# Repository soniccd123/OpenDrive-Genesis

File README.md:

# OpenDrive-Genesis
A open hardware flashcart for the Sega Genesis/32X

This project was born as way to use 3.3V parts safely for repro carts but, with the use o Flash memory, the read/write potencial of the ROM made me develop it to another direction: A Flashcart

This is quite a barebones Flashcart, nothing compared to Krizz's Everdrive ease of use. It is intended for DIY entusiasts, as learning platform and maybe as a starting point for me and other people projects. This is Open Hardware, do whatever it pleases you with it, I'm happy to help as needed.

As of now, these are its features:

- Suports Genesis and 32X software
- ROM Support for up to 4MB
- Save support for all ROM sizes (Selection for <2MB/>2MB by jumper)
- 32KB of FeRAM for saving
- No need for battery for saving
- Safe 3.3V to 5V level-shifting

What it doesnt do compared to commercially available carts:
- Multiple ROMs at the same time;
- ROM menu;
- SD support;
- Needs a programmer (The OpenDrive Programmer)
- Does not support Sega CD games and special chips (and probably never will);

This project is possible thanks to TmEE (NESdev Forums, SRAM wiring schematics), Rene Richard (db-electronics on GitHUB, KiCAD libs for the Genesis cart connector), lidnariq (NESdev Forums, Safe level-shifting), Ziggy587 (Racketboy, ideas, sugestions, support and encouragement), The Racketboy and NESdev forums.

# Other projects of the same family
- OpenDrive Programmer: https://github.com/soniccd123/OpenDrive-Programmer
- OpenDrive Programmer firmware: https://github.com/soniccd123/OpenDrive-Programmer-firmware
- OpenDrive Editor: https://github.com/soniccd123/OpenDrive-Editor

# Building the cartridge
I recommend that the release folder is used, the Bill of Materials is contained in the CSV file. The develop folder also works and its the actually tested cart by me, it only has aditional footprints for a being tested bank switching circuit.

The FM1808 is also not strictly necessary if you don't plan to save your games. The 74HC74 and the 74HC139 are still necessary in this case for the correct CE signaling.

You must short the JP1 jumper acordinly to the type of games you're going to use:
- For save support on <2MB games, short pins 1 and 2 (<2MB on the cart);
- For save support on >2MB games, short pins 3 and 2 (>2MB on the cart);
- If the save support is not necessary and the FM1808 is not soldered, short the 3 and 2 pins (>2MB on the cart).

With this the cart should be ready for writing and playing!

# Documentation
- Technical Manual, in constant work, sugestions welcome: https://docs.google.com/document/d/e/2PACX-1vTHuY665FCTQgpWVqtx0Hk3dTyNgIxMEns0RzGF2l86pw4OjIR6taxs3owxL13b5aOQaE71-1f7qCdJ/pub
- MX29L3211 Datasheet: http://www.wolfgangrobel.de/electronics/datasheets/eprom/MX29L3211.pdf
- FM1808 Datasheet: https://datasheet.octopart.com/FM1808-70-PG-Ramtron-datasheet-8328945.pdf
- 74HC74 Datasheet: https://assets.nexperia.com/documents/data-sheet/74HC_HCT74.pdf
- 74HC139 Datasheet https://assets.nexperia.cn/documents/data-sheet/74HC_HCT139.pdf
- 74LVC8T245 Datasheet: https://assets.nexperia.com/documents/data-sheet/74LVC_LVCH8T245.pdf

# Disclaimer
I'm not a professional hardware engineer, while this flashcart was designed to be the safest possible to your console, I'm not responsible for any damages done if used or built wrong. Also, revise the design always before building the PCB, I'm a amateur human and errors may have been commited. It you spot anything, hit me with a message and I will happily fix that. Also, any sugestions are welcome!

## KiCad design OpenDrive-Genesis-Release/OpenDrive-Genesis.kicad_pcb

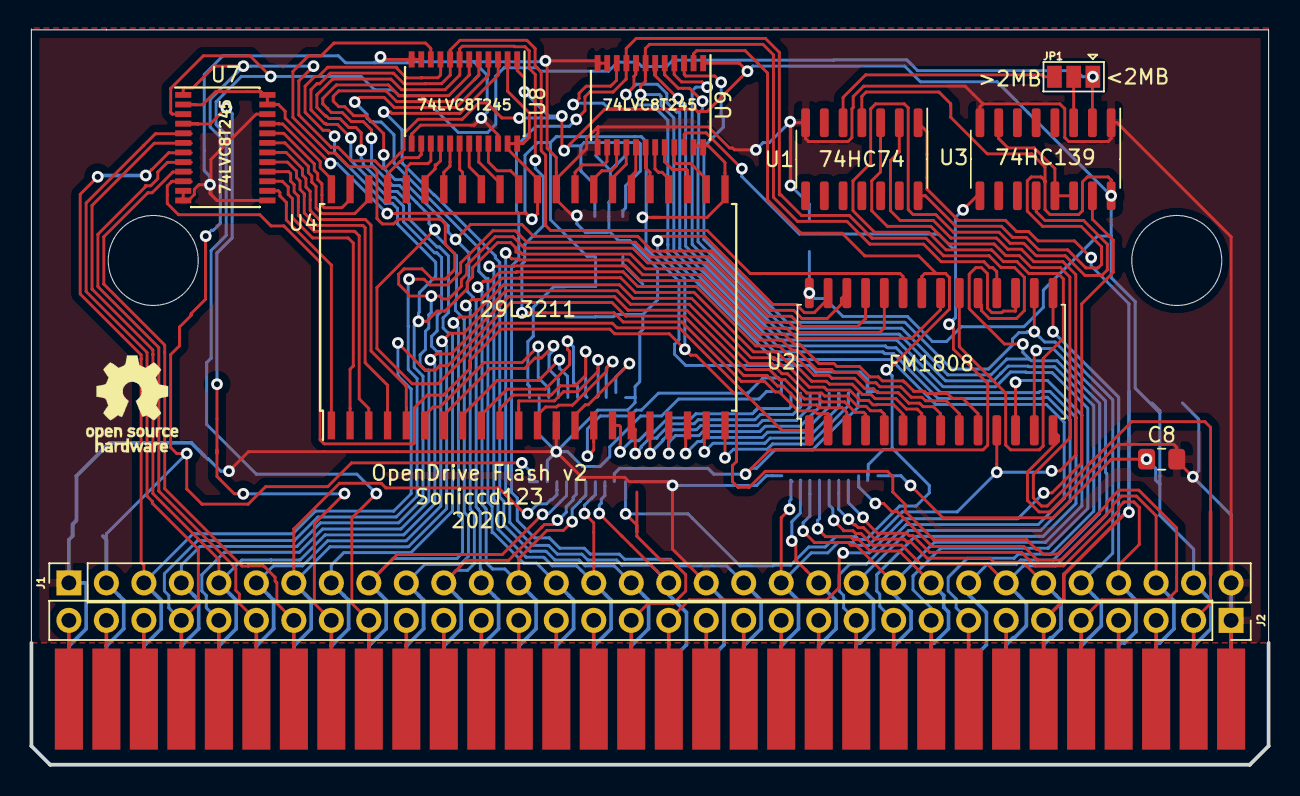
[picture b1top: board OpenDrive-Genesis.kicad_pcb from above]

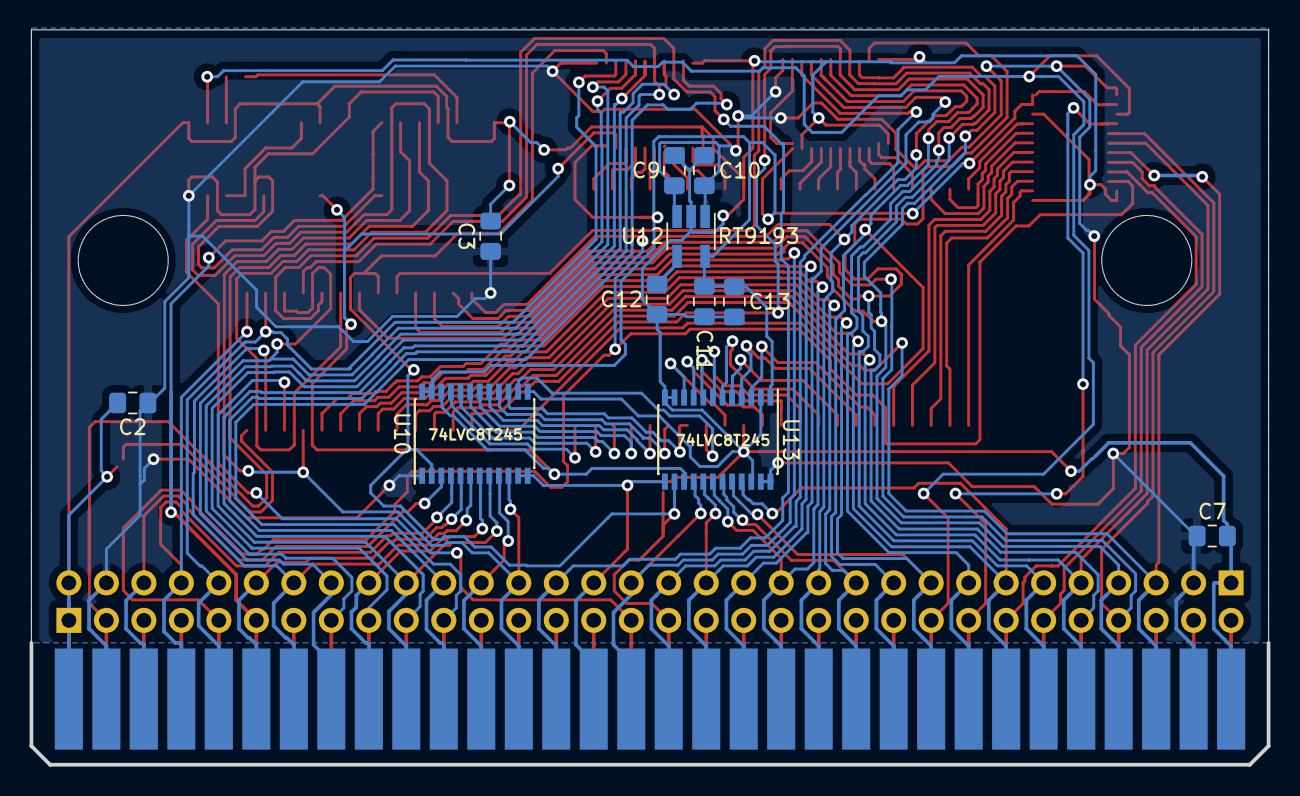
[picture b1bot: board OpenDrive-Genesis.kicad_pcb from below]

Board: 2 copper layers, 83.8 x 49.7 mm, 23 parts (11 on the bottom side), 107 nets.

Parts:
C2, C3, C7, C8, C9, C13: 100nF; C_0805_2012Metric_Pad1.15x1.40mm_HandSolder
C10, C11: 10uF; C_0805_2012Metric_Pad1.15x1.40mm_HandSolder
C12: 1uF; C_0805_2012Metric_Pad1.15x1.40mm_HandSolder
CON1: GENESIS-EDGE
J1, J2: Conn_01x32_Male; PinSocket_1x32_P2.54mm_Vertical
JP1: <2M/4M; SolderJumper-3_P1.3mm_Open_Pad1.0x1.5mm
U1: 74HC74; SOIC-14_3.9x8.7mm_P1.27mm
U2: FM1808B-SG; SOIC-28W_7.5x17.9mm_P1.27mm
U3: 74LS139; SOIC-16_3.9x9.9mm_P1.27mm
U4: 29L3211; PSOP-44_16.9x27.17mm_P1.27mm
U7, U8, U9, U10, U13: 74LVC8T245; TSSOP-24_4.4x7.8mm_P0.65mm
U12: RT9193; SOT-23-5_HandSoldering

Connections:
+3V3: C11.2, C13.2, U4.23, U4.33, U7.2, U7.23, U7.24, U8.2, U8.23, U8.24, U9.23, U9.24, U10.23, U10.24, U12.5, U13.1
+5V: C2.1, C3.1, C7.1, C8.1, C9.1, C10.1, CON1.A2, CON1.A31, J1.2, J1.31, U1.4, U1.14, U2.28, U3.16, U7.1, U8.1, U9.1, U10.1, U12.1, U12.3, U13.23, U13.24
/3V_CE: U4.12, U13.9
/3V_OE: U4.14, U13.10
/3V_WE: U4.1, U7.14
/A0: CON1.A17, J1.17, U2.10, U13.16
/A1: CON1.A15, J1.15, U2.9, U13.17
/A2: CON1.A13, J1.13, U2.8, U13.18
/A3: CON1.A11, J1.11, U2.7, U13.19
/A4: CON1.A9, J1.9, U2.6, U13.20
/A5: CON1.A7, J1.7, U2.5, U13.21
/A6: CON1.A5, J1.5, U2.4, U7.6
/A7: CON1.A3, J1.3, U2.3, U7.7
/A8: CON1.B4, J2.29, U2.25, U7.5
/A9: CON1.B5, J2.28, U2.24, U8.10
/A10: CON1.A4, J1.4, U2.21, U8.9
/A11: CON1.A6, J1.6, U2.23, U8.8
/A12: CON1.A8, J1.8, U2.2, U8.7
/A15: CON1.A14, J1.14, U8.4
/A16: CON1.A16, J1.16, U8.3
/A17: CON1.B6, J2.27, U7.8
/A18: CON1.B7, J2.26, U7.9
/CART_A13: CON1.A10, J1.10, U2.1, U8.6
/CART_A14: CON1.A12, J1.12, U2.26, U8.5
/CART_A19: CON1.B8, J2.25, U7.4
/CART_A20: CON1.B9, J2.24, JP1.1, U3.2, U7.3
/CE: CON1.B17, J2.16, U3.15
/D0: CON1.A20, J1.20, U1.2, U2.11, U10.10
/D1: CON1.A23, J1.23, U2.12, U10.8
/D2: CON1.A26, J1.26, U2.13, U10.6
/D3: CON1.A29, J1.29, U2.15, U10.4
/D4: CON1.A28, J1.28, U2.16, U9.3
/D5: CON1.A25, J1.25, U2.17, U9.5
/D6: CON1.A22, J1.22, U2.18, U9.7
/D7: CON1.A19, J1.19, U2.19, U9.9
/D8: CON1.A21, J1.21, U10.9
/D9: CON1.A24, J1.24, U10.7
/D10: CON1.A27, J1.27, U10.5
/D11: CON1.A30, J1.30, U10.3
/D12: CON1.B25, J2.8, U9.4
/D13: CON1.B24, J2.9, U9.6
/D14: CON1.B23, J2.10, U9.8
/D15: CON1.B22, J2.11, U9.10
/OE: CON1.B16, J2.17, U2.22, U9.2, U10.2, U13.14
/RESET: CON1.B27, J2.6, U1.1
/ROM_A0: U4.11, U13.8
/ROM_A1: U4.10, U13.7
/ROM_A2: U4.9, U13.6
/ROM_A3: U4.8, U13.5
/ROM_A4: U4.7, U13.4
/ROM_A5: U4.6, U13.3
/ROM_A6: U4.5, U7.18
/ROM_A7: U4.4, U7.17
/ROM_A8: U4.42, U7.19
/ROM_A9: U4.41, U8.14
/ROM_A10: U4.40, U8.15
/ROM_A11: U4.39, U8.16
/ROM_A12: U4.38, U8.17
/ROM_A13: U4.37, U8.18
/ROM_A14: U4.36, U8.19
/ROM_A15: U4.35, U8.20
/ROM_A16: U4.34, U8.21
/ROM_A17: U4.3, U7.16
/ROM_A18: U4.2, U7.15
/ROM_A19: U4.43, U7.20
/ROM_A20: U4.44, U7.21
/ROM_CE: U3.9, U9.22, U10.22, U13.15
/ROM_D0: U4.15, U10.14
/ROM_D1: U4.17, U10.16
/ROM_D2: U4.19, U10.18
/ROM_D3: U4.21, U10.20
/ROM_D4: U4.24, U9.21
/ROM_D5: U4.26, U9.19
/ROM_D6: U4.28, U9.17
/ROM_D7: U4.30, U9.15
/ROM_D8: U4.16, U10.15
/ROM_D9: U4.18, U10.17
/ROM_D10: U4.20, U10.19
/ROM_D11: U4.22, U10.21
/ROM_D12: U4.25, U9.20
/ROM_D13: U4.27, U9.18
/ROM_D14: U4.29, U9.16
/ROM_D15: U4.31, U9.14
/SRAM_CE: U2.20, U3.12
/TIME: CON1.B31, J2.2, U1.3
/WE: CON1.B28, J2.5, U2.27, U7.10
GND: C2.2, C3.2, C7.2, C8.2, C9.2, C10.2, C11.1, C12.2, C13.1, CON1.A1, CON1.A18, CON1.A32, CON1.B32, J1.1, J1.18, J1.32, J2.1, U1.7, U2.14, U3.1, U3.8, U4.13, U4.32, U7.11, U7.12, U7.13, U7.22, U8.11, U8.12, U8.13, U8.22, U9.11, U9.12, U9.13, U10.11, U10.12, U10.13, U12.2, U13.2, U13.11, U13.12, U13.13, U13.22
unnamed: C12.1, U12.4
unnamed: CON1.B1, J2.32
unnamed: CON1.B2, J2.31
unnamed: CON1.B3, J2.30
unnamed: CON1.B10, J2.23
unnamed: CON1.B11, J2.22
unnamed: CON1.B12, J2.21
unnamed: CON1.B13, J2.20
unnamed: CON1.B14, J2.19
unnamed: CON1.B15, J2.18
unnamed: CON1.B18, J2.15
unnamed: CON1.B19, J2.14
unnamed: CON1.B20, J2.13
unnamed: CON1.B21, J2.12
unnamed: CON1.B26, J2.7
unnamed: CON1.B29, J2.4
unnamed: CON1.B30, J2.3
unnamed: JP1.2, U3.3
unnamed: JP1.3, U1.5
unnamed: U3.7, U3.13, U3.14

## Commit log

2021-02-27 Change structure, divided in realease and development folders
